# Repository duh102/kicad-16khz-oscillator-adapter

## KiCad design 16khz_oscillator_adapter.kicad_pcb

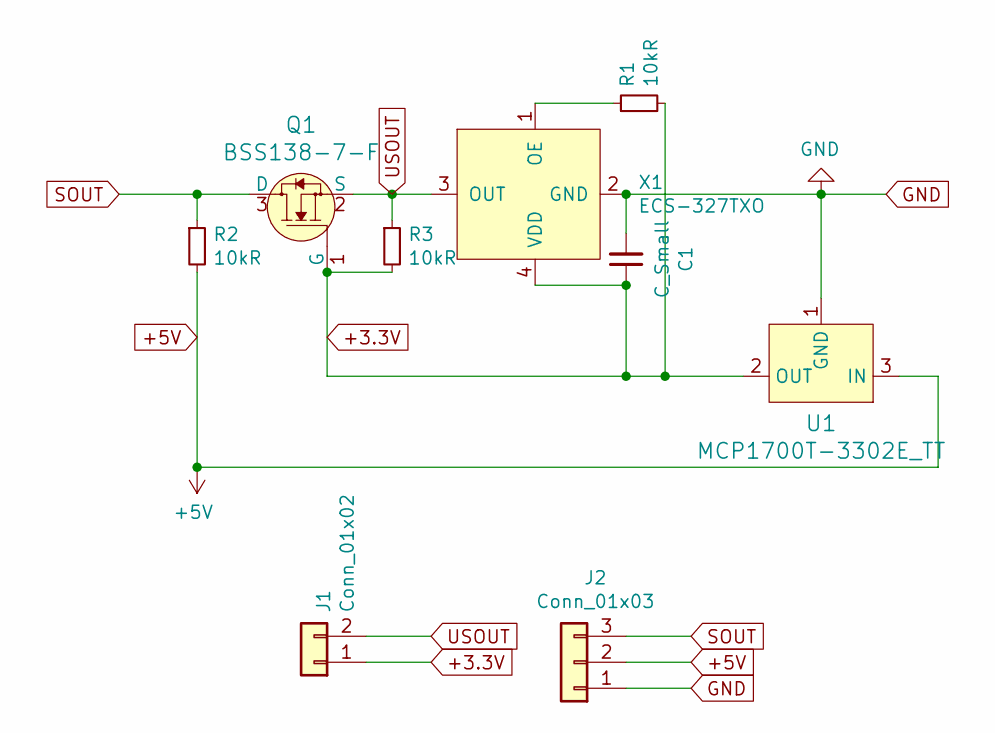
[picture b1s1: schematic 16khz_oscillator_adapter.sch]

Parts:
C1: C_Small; C_0805_2012Metric
J1: Conn_01x02; PinHeader_1x02_P2.54mm_Vertical
J2: Conn_01x03; PinHeader_1x03_P2.54mm_Vertical
Q1: BSS138-7-F; SOT-23-3; MPN BSS138-7-F; Digi-Key_PN BSS138-FDICT-ND
R1, R2, R3: 10kR; R_0805_2012Metric
U1: MCP1700T-3302E_TT; SOT-23-3; MPN MCP1700T-3302E/TT; Digi-Key_PN MCP1700T3302ETTCT-ND
X1: ECS-327TXO; ECS-327MVATX-3

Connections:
+3.3V: C1.1, J1.1, Q1.1 (G), R1.2, R3.2, U1.2 (OUT), X1.4 (VDD)
+5V: J2.2, R2.2, U1.3 (IN)
GND: C1.2, J2.1, U1.1 (GND), X1.2 (GND)
unnamed: R1.1, X1.1 (OE)
SOUT: J2.3, Q1.3 (D), R2.1
USOUT: J1.2, Q1.2 (S), R3.1, X1.3 (OUT)

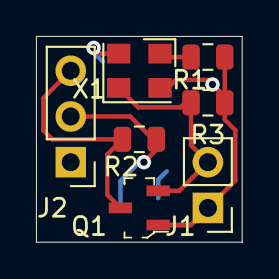
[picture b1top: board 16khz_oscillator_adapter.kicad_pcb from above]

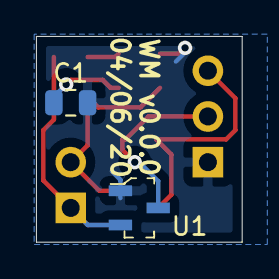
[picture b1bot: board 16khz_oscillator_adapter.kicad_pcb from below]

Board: 2 copper layers, 11.4 x 11.4 mm, 9 parts (2 on the bottom side), 6 nets.

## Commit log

2020-04-07 Add gerber output
2020-12-09 Update gitignore
